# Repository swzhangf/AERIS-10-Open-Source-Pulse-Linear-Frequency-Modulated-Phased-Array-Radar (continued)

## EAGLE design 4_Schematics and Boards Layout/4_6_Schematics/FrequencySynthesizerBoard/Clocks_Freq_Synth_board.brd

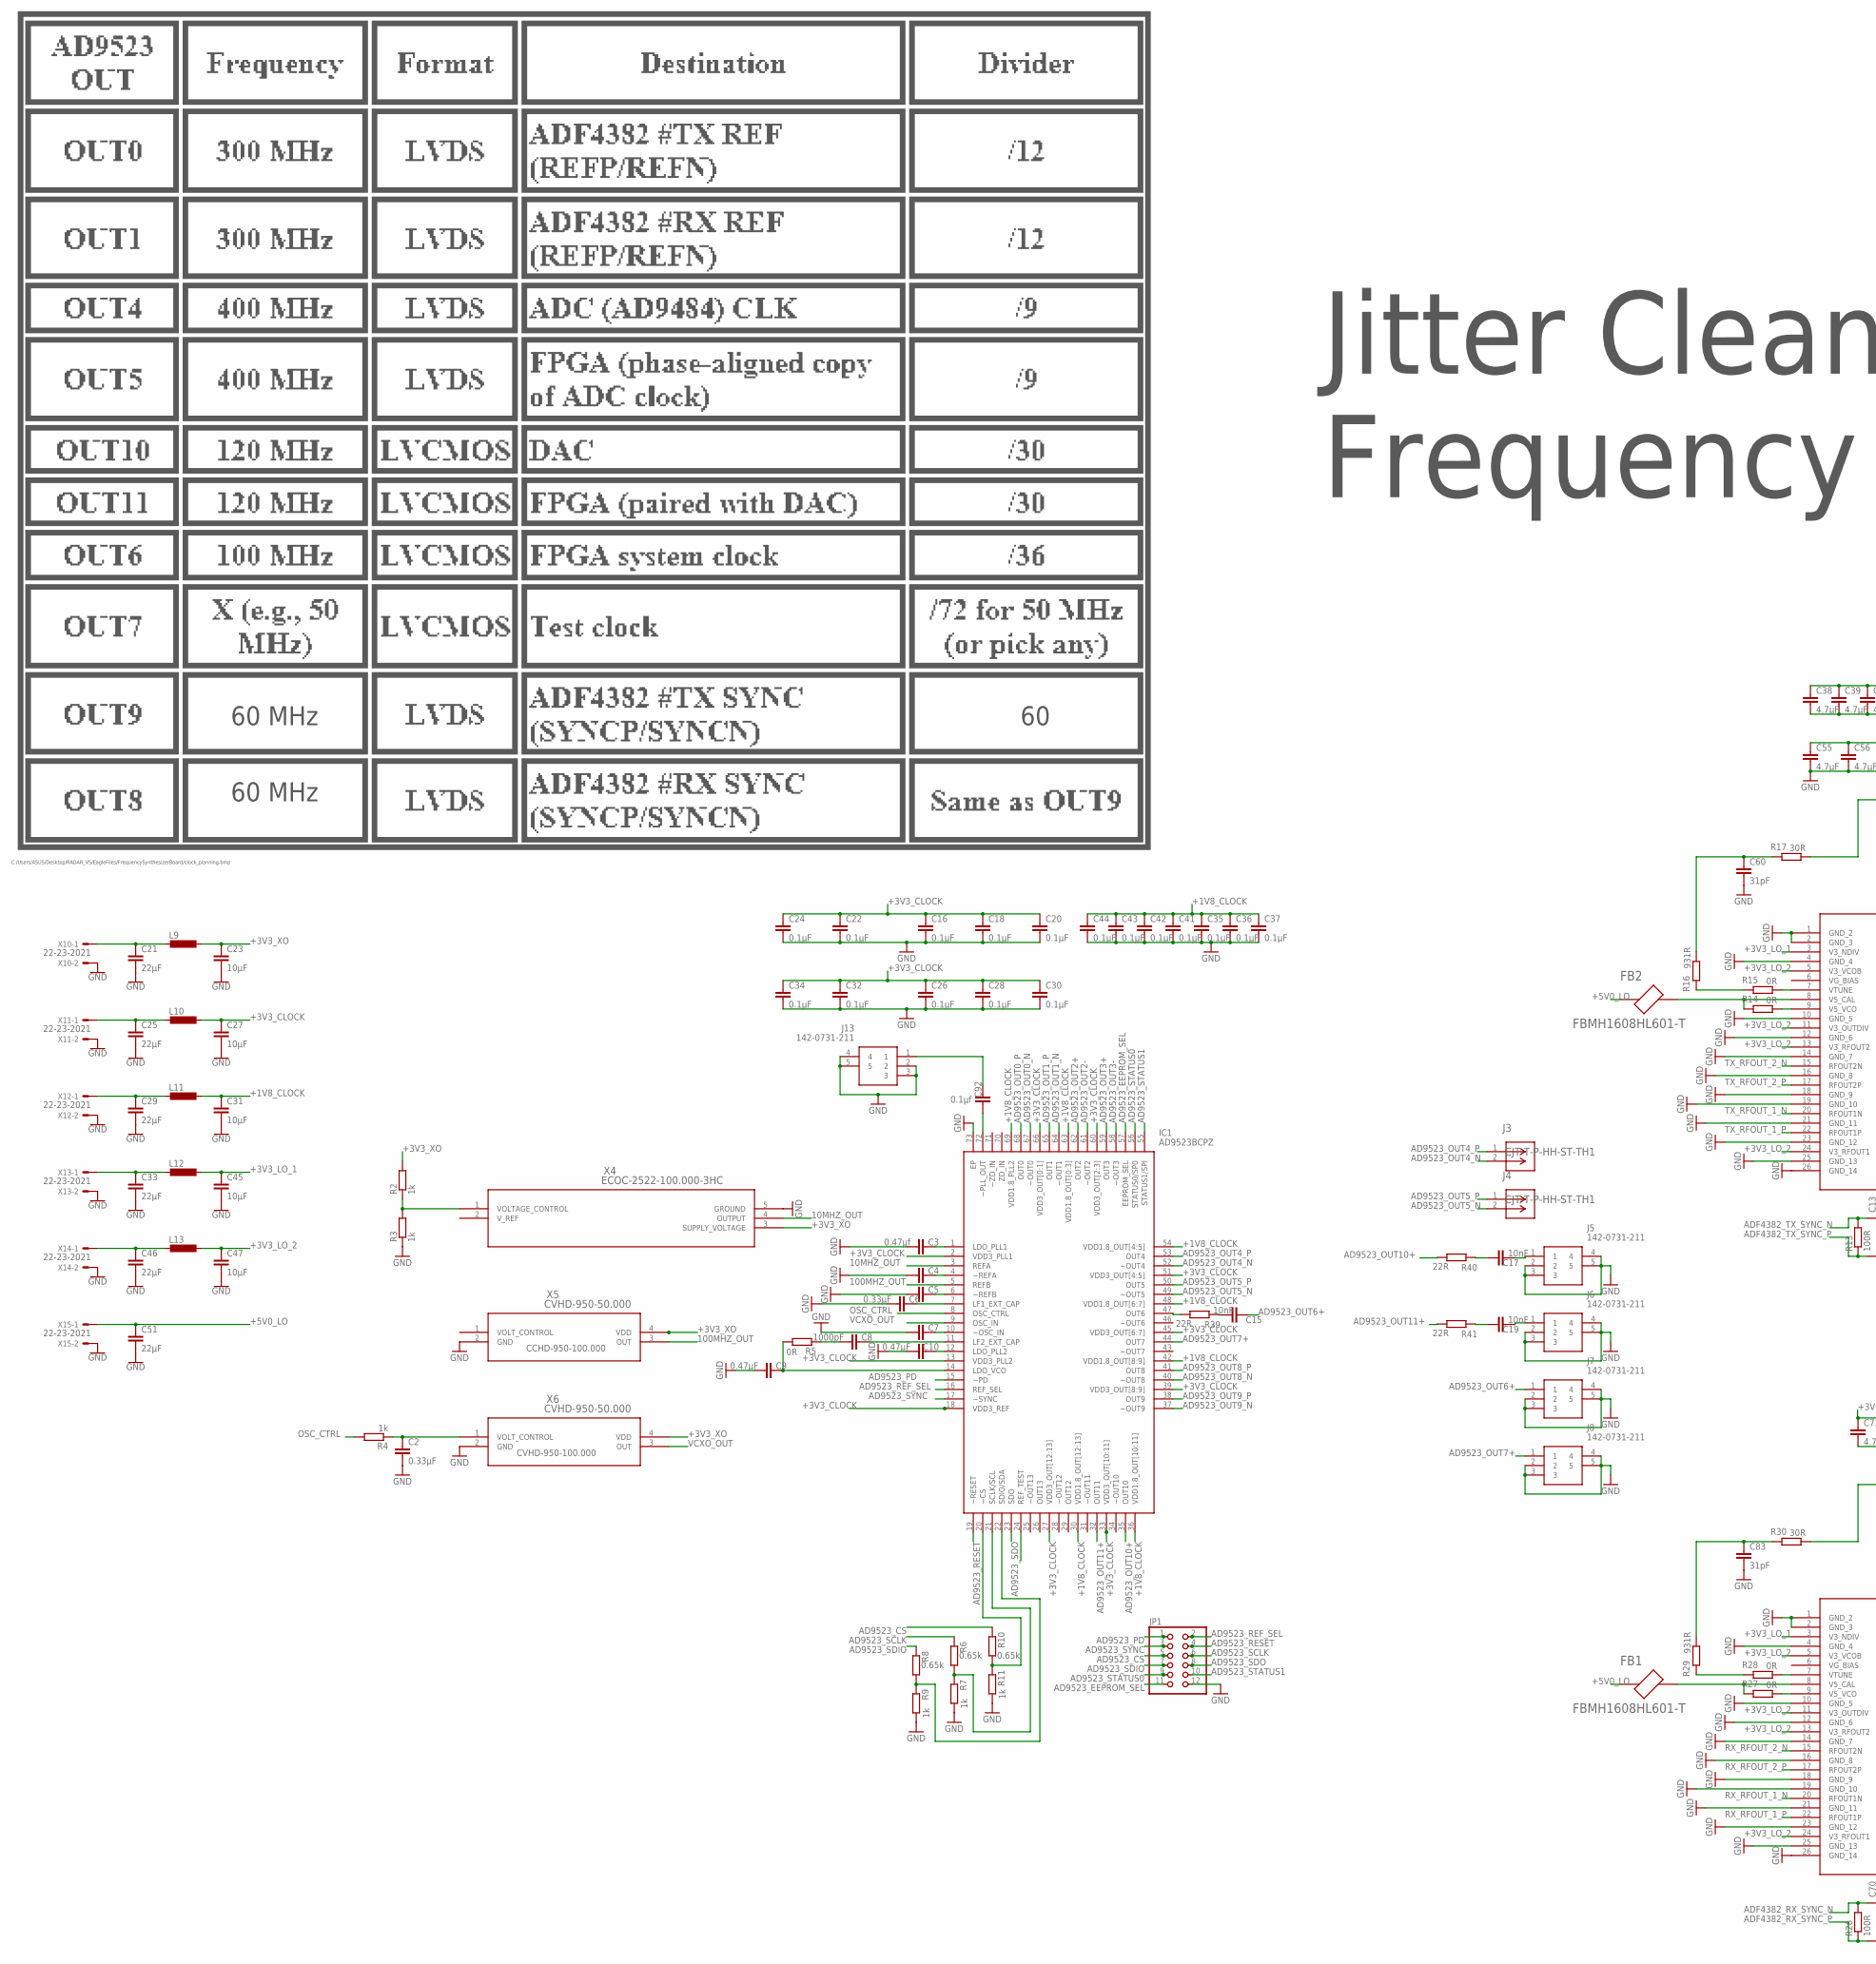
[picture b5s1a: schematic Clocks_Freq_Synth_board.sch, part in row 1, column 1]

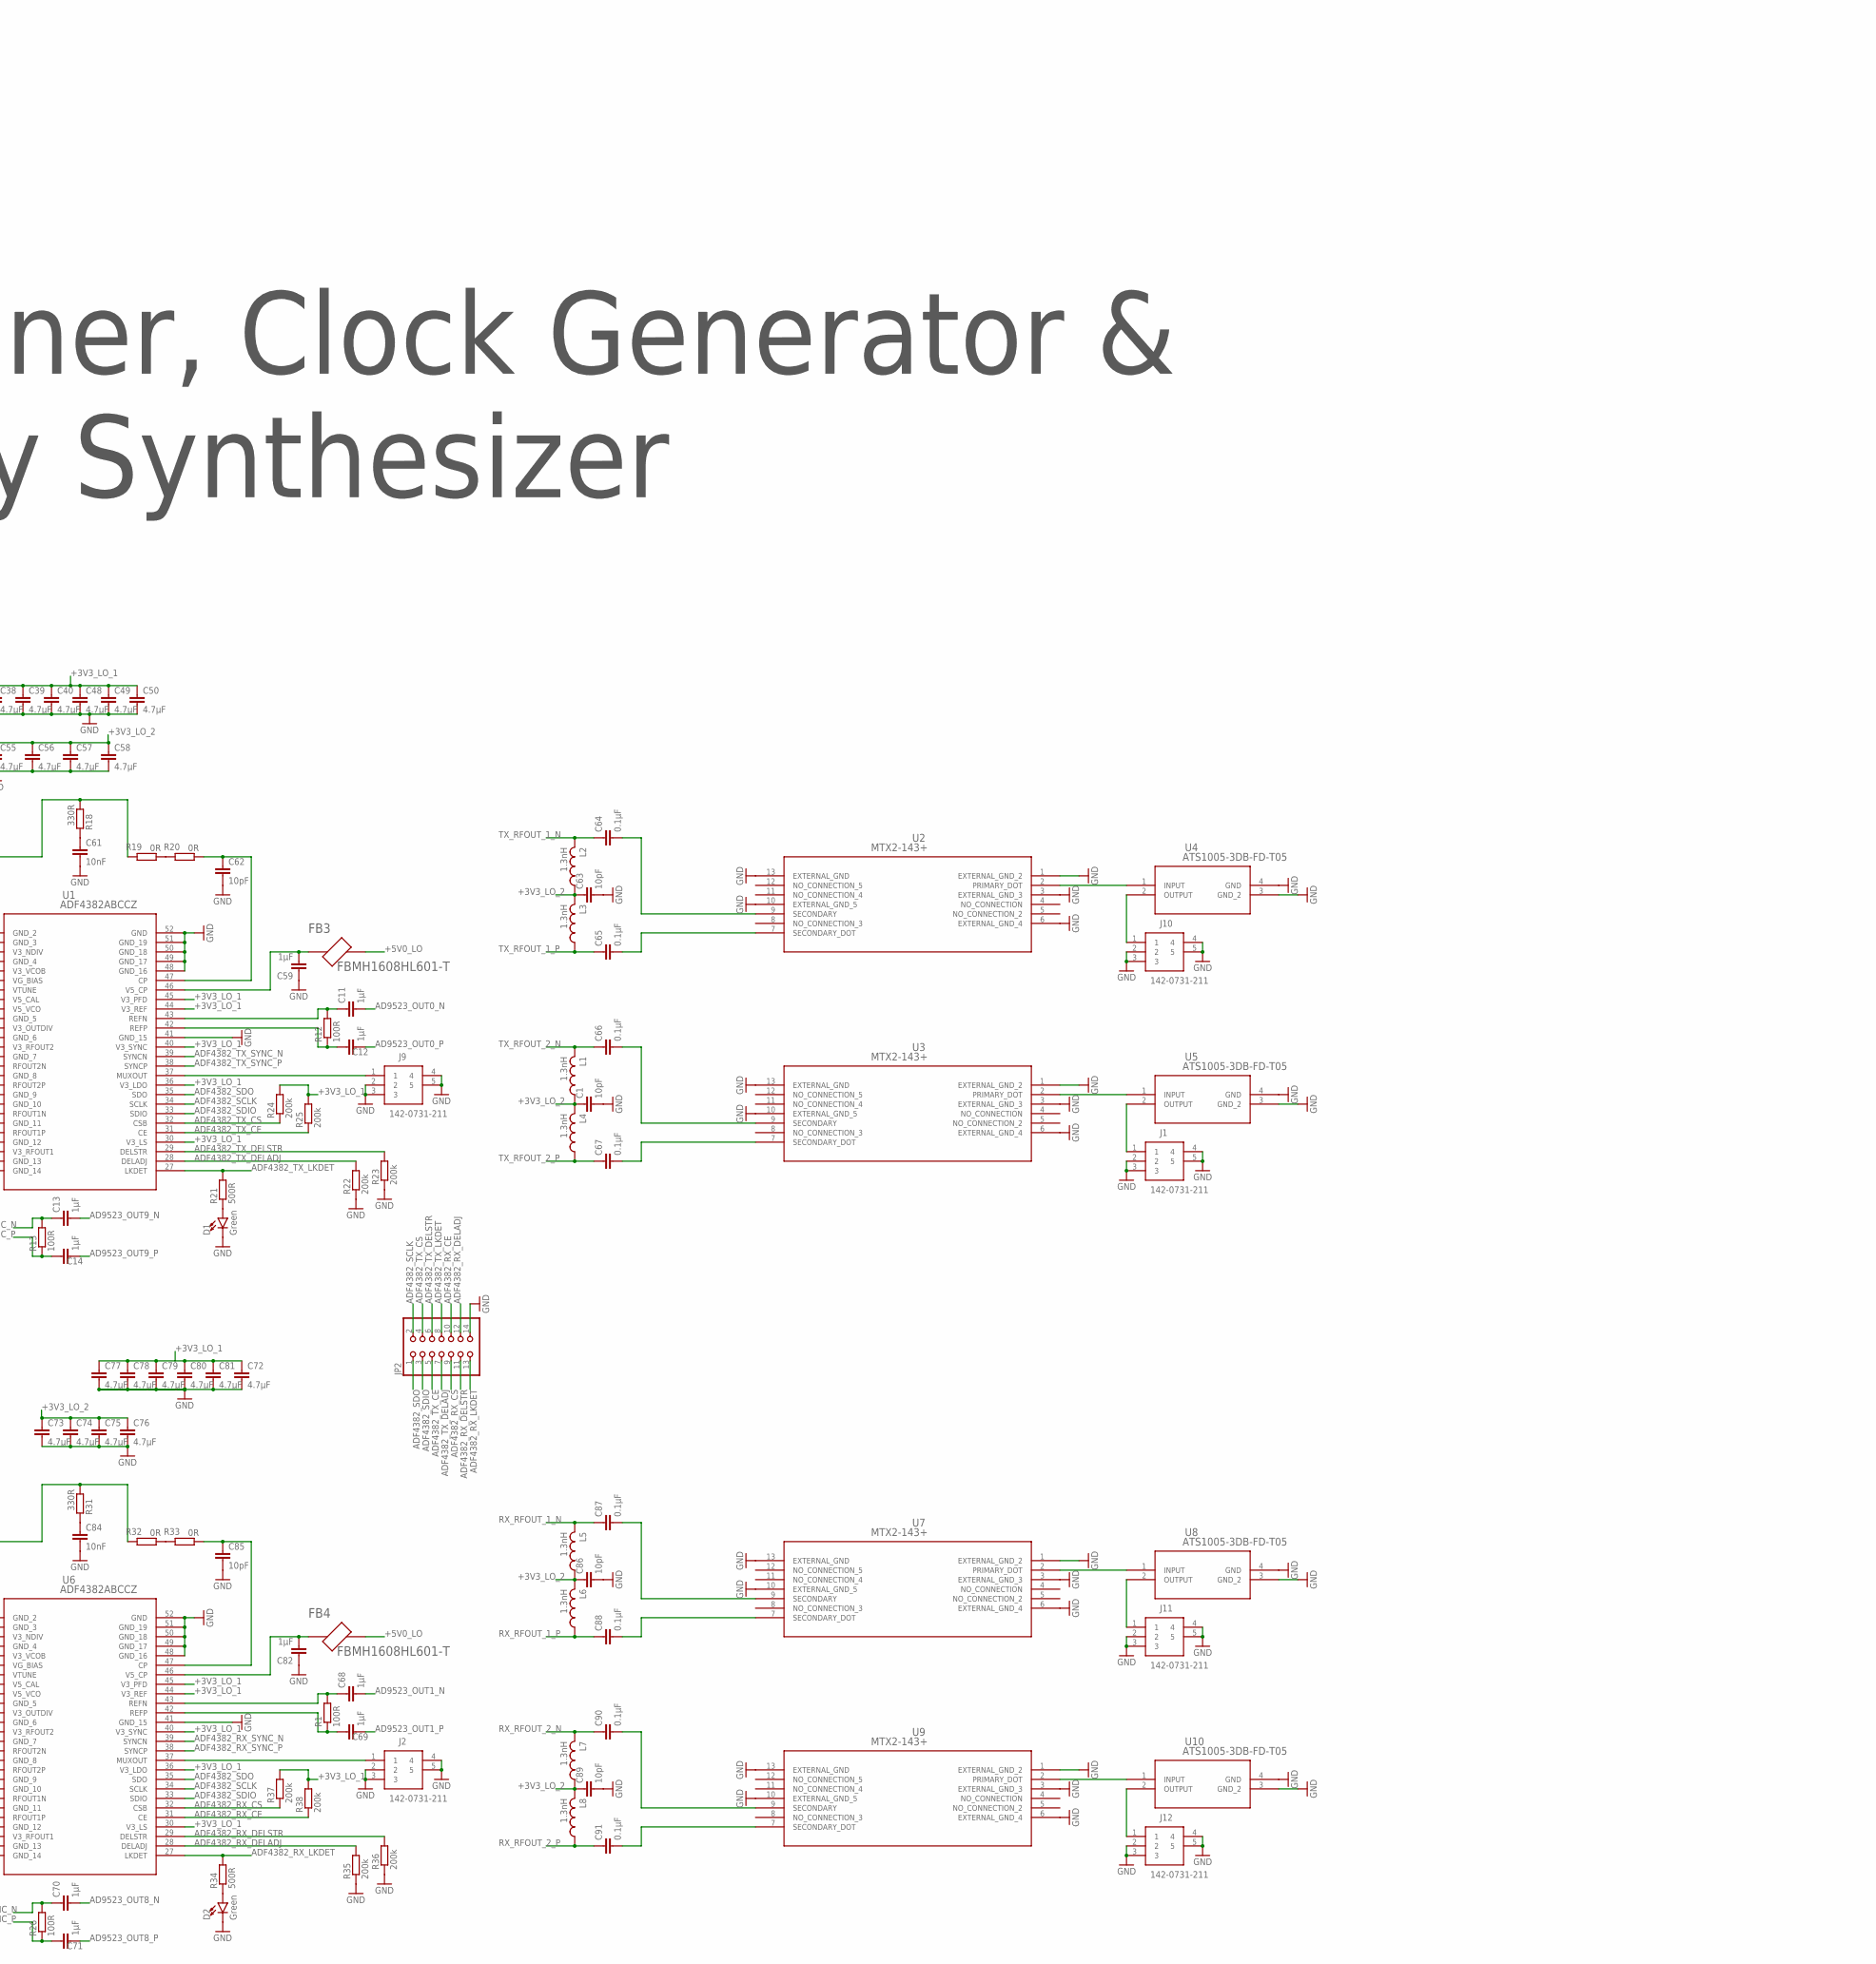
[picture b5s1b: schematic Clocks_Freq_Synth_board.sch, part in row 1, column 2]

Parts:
C1, C62, C63, C85, C86, C89: 10pF; C0201
C2, C6: 0.33µF; C0201
C3: 0.47µf; C0201
C4, C5, C7: C-EUC0201; C0201
C8: 1000pF; C0201
C9, C10: 0.47µF; C0201
C11, C12, C13, C14, C59, C68, C69, C70, C71, C82: 1µF; C0201
C15, C17, C19: 10nF; C0402
C16, C18, C20, C22, C24, C26, C28, C30, C32, C34, C35, C36, C37, C41, C42, C43, C44, C64, C65, C66, C67, C87, C88, C90, C91: 0.1µF; C0201
C21, C25, C29, C33, C46, C51: 22µF; C1210
C23, C27, C31, C45, C47: 10µF; C1210
C38, C39, C40, C48, C49, C50, C55, C56, C57, C58, C72, C73, C74, C75, C76, C77, C78, C79, C80, C81: 4.7µF; C0201
C60, C83: 31pF; C0201
C61, C84: 10nF; C0201
C92: 0.1µf; C0201
D1, D2: Green; LED-0603
FB1, FB2, FB3, FB4: FBMH1608HL601-T; BEADC1608X90N
IC1: AD9523BCPZ; QFN50P1000X1000X100-73N
J1, J2, J5, J6, J7, J8, J9, J10, J11, J12, J13: 142-0731-211; 1420731211
J3, J4: CJT-T-P-HH-ST-TH1; CONN_CJT-T-P-XX-ST-TH1_SAI
JP1: PINHD-2X6; 2X06
JP2: PINHD-2X7; 2X07
L1, L2, L3, L4, L5, L6, L7, L8: 1.3nH; L0201
L9, L10, L11, L12, L13: L-EUL5650M; L5650M
R1, R12, R13, R26: 100R; R0201
R2, R3, R4, R7, R9, R11: 1k; R0201
R5, R14, R15, R19, R20, R27, R28, R32, R33: 0R; R0201
R6, R8, R10: 0.65k; R0201
R16, R29: 931R; R0201
R17, R30: 30R; R0201
R18, R31: 330R; R0201
R21, R34: 500R; R0201
R22, R23, R24, R25, R35, R36, R37, R38: 200k; R0201
R39, R40, R41: 22R; R0201
U1, U6: ADF4382ABCCZ; CC-48-10_ADI
U2, U3, U7, U9: MTX2-143+; DQ1225_MNC
U4, U5, U8, U10: ATS1005-3DB-FD-T05; SMT_DB-FD-T05_SUS
X4: ECOC-2522-100.000-3HC; SMD5_ECOC-2522_25P4X22_ECS
X5, X6: CVHD-950-50.000; SMD4_CVHD-950_CRX
X10, X11, X12, X13, X14, X15: 22-23-2021

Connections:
10MHZ_OUT: IC1.3 (REFA), X4.4 (OUTPUT)
100MHZ_OUT: IC1.5 (REFB), X5.3 (OUT)
+1V8_CLOCK: C31.1, C35.1, C36.1, C37.1, C41.1, C42.1, C43.1, C44.1, IC1.30 (VDD1.8_OUT[12:13]), IC1.36 (VDD1.8_OUT[10:11]), IC1.42 (VDD1.8_OUT[8:9]), IC1.48 (VDD1.8_OUT[6:7]), IC1.54 (VDD1.8_OUT[4:5]), IC1.63 (VDD1.8_OUT[0:3]), IC1.69 (VDD1.8_PLL2), L11.1
+3V3_CLOCK: C16.1, C18.1, C20.1, C22.1, C24.1, C26.1, C27.1, C28.1, C30.1, C32.1, C34.1, IC1.2 (VDD3_PLL1), IC1.13 (VDD3_PLL2), IC1.18 (VDD3_REF), IC1.27 (VDD3_OUT[12:13]), IC1.33 (VDD3_OUT[10:11]), IC1.39 (VDD3_OUT[8:9]), IC1.45 (VDD3_OUT[6:7]), IC1.51 (VDD3_OUT[4:5]), IC1.60 (VDD3_OUT[2:3]), IC1.66 (VDD3_OUT[0:1]), L10.1
+3V3_LO_1: C38.1, C39.1, C40.1, C45.1, C48.1, C49.1, C50.1, C72.1, C77.1, C78.1, C79.1, C80.1, C81.1, L12.1, R24.2, R25.2, R37.2, R38.2, U1.3 (V3_NDIV), U1.30 (V3_LS), U1.36 (V3_LDO), U1.40 (V3_SYNC), U1.44 (V3_REF), U1.45 (V3_PFD), U6.3 (V3_NDIV), U6.30 (V3_LS), U6.36 (V3_LDO), U6.40 (V3_SYNC), U6.44 (V3_REF), U6.45 (V3_PFD)
+3V3_LO_2: C1.1, C47.1, C55.1, C56.1, C57.1, C58.1, C63.1, C73.1, C74.1, C75.1, C76.1, C86.1, C89.1, L1.1, L2.1, L3.2, L4.2, L5.1, L6.2, L7.1, L8.2, L13.1, U1.5 (V3_VCOB), U1.11 (V3_OUTDIV), U1.13 (V3_RFOUT2), U1.24 (V3_RFOUT1), U6.5 (V3_VCOB), U6.11 (V3_OUTDIV), U6.13 (V3_RFOUT2), U6.24 (V3_RFOUT1)
+3V3_XO: C23.1, L9.1, R2.2, X4.3 (SUPPLY_VOLTAGE), X5.4 (VDD), X6.4 (VDD)
+5V0_LO: C51.1, FB1.1, FB2.1, FB3.2, FB4.2, X15.1
AD9523_CS: JP1.5, R10.1
AD9523_EEPROM_SEL: IC1.57 (EEPROM_SEL), JP1.11
AD9523_OUT0_N: C11.2, IC1.67 (~OUT0)
AD9523_OUT0_P: C12.2, IC1.68 (OUT0)
AD9523_OUT1_N: C68.2, IC1.64 (~OUT1)
AD9523_OUT1_P: C69.2, IC1.65 (OUT1)
AD9523_OUT2+: IC1.62 (OUT2)
AD9523_OUT2-: IC1.61 (~OUT2)
AD9523_OUT3+: IC1.59 (OUT3)
AD9523_OUT3-: IC1.58 (~OUT3)
AD9523_OUT4_N: IC1.52 (~OUT4), J3.2
AD9523_OUT4_P: IC1.53 (OUT4), J3.1
AD9523_OUT5_N: IC1.49 (~OUT5), J4.2
AD9523_OUT5_P: IC1.50 (OUT5), J4.1
AD9523_OUT6+: C15.2, J7.1
AD9523_OUT7+: IC1.44 (OUT7), J8.1
AD9523_OUT8_N: C70.2, IC1.40 (~OUT8)
AD9523_OUT8_P: C71.2, IC1.41 (OUT8)
AD9523_OUT9_N: C13.2, IC1.37 (~OUT9)
AD9523_OUT9_P: C14.2, IC1.38 (OUT9)
AD9523_OUT10+: IC1.35 (OUT10), R40.1
AD9523_OUT11+: IC1.32 (OUT11), R41.1
AD9523_PD: IC1.15 (~PD), JP1.1
AD9523_REF_SEL: IC1.16 (REF_SEL), JP1.2
AD9523_RESET: IC1.19 (~RESET), JP1.4
AD9523_SCLK: JP1.6, R6.1
AD9523_SDIO: JP1.7, R8.1
AD9523_SDO: IC1.23 (SDO), JP1.8
AD9523_STATUS0: IC1.56 (STATUS0/SP0), JP1.9
AD9523_STATUS1: IC1.55 (STATUS1/SPI), JP1.10
AD9523_SYNC: IC1.17 (~SYNC), JP1.3
ADF4382_RX_CE: JP2.10, R38.1, U6.31 (CE)
ADF4382_RX_CS: JP2.9, R37.1, U6.32 (CSB)
ADF4382_RX_DELADJ: JP2.12, R35.2, U6.28 (DELADJ)
ADF4382_RX_DELSTR: JP2.11, R36.2, U6.29 (DELSTR)
ADF4382_RX_LKDET: JP2.13, R34.2, U6.27 (LKDET)
ADF4382_RX_SYNC_N: C70.1, R26.2, U6.39 (SYNCN)
ADF4382_RX_SYNC_P: C71.1, R26.1, U6.38 (SYNCP)
ADF4382_SCLK: JP2.2, U1.34 (SCLK), U6.34 (SCLK)
ADF4382_SDIO: JP2.3, U1.33 (SDIO), U6.33 (SDIO)
ADF4382_SDO: JP2.1, U1.35 (SDO), U6.35 (SDO)
ADF4382_TX_CE: JP2.5, R25.1, U1.31 (CE)
ADF4382_TX_CS: JP2.4, R24.1, U1.32 (CSB)
ADF4382_TX_DELADJ: JP2.7, R22.2, U1.28 (DELADJ)
ADF4382_TX_DELSTR: JP2.6, R23.2, U1.29 (DELSTR)
ADF4382_TX_LKDET: JP2.8, R21.2, U1.27 (LKDET)
ADF4382_TX_SYNC_N: C13.1, R13.2, U1.39 (SYNCN)
ADF4382_TX_SYNC_P: C14.1, R13.1, U1.38 (SYNCP)
GND: C1.2, C2.2, C3.1, C4.1, C5.1, C6.1, C7.1, C9.1, C10.1, C16.2, C18.2, C20.2, C21.2, C22.2, C23.2, C24.2, C25.2, C26.2, C27.2, C28.2, C29.2, C30.2, C31.2, C32.2, C33.2, C34.2, C35.2, C36.2, C37.2, C38.2, C39.2, C40.2, C41.2, C42.2, C43.2, C44.2, C45.2, C46.2, C47.2, C48.2, C49.2, C50.2, C51.2, C55.2, C56.2, C57.2, C58.2, C59.1, C60.2, C61.2, C62.2, C63.2, C72.2, C73.2, C74.2, C75.2, C76.2, C77.2, C78.2, C79.2, C80.2, C81.2, C82.1, C83.2, C84.2, C85.2, C86.2, C89.2, D1.C, D2.C, IC1.73 (EP), J1.2, J1.3, J1.4, J1.5, J2.2, J2.3, J2.4, J2.5, J5.2, J5.3, J5.4, J5.5, J6.2, J6.3, J6.4, J6.5, J7.2, J7.3, J7.4, J7.5, J8.2, J8.3, J8.4, J8.5, J9.2, J9.3, J9.4, J9.5, J10.2, J10.3, J10.4, J10.5, J11.2, J11.3, J11.4, J11.5, J12.2, J12.3, J12.4, J12.5, J13.2, J13.3, J13.4, J13.5, JP1.12, JP2.14, R3.1, R7.2, R9.2, R11.2, R22.1, R23.1, R35.1, R36.1, U1.1 (GND_2), U1.2 (GND_3), U1.4 (GND_4), U1.10 (GND_5), U1.12 (GND_6), U1.14 (GND_7), U1.16 (GND_8), U1.18 (GND_9), U1.19 (GND_10), U1.21 (GND_11), U1.23 (GND_12), U1.25 (GND_13), U1.26 (GND_14), U1.41 (GND_15), U1.48 (GND_16), U1.49 (GND_17), U1.50 (GND_18), U1.51 (GND_19), U1.52 (GND), U2.1 (EXTERNAL_GND_2), U2.3 (EXTERNAL_GND_3), U2.6 (EXTERNAL_GND_4), U2.10 (EXTERNAL_GND_5), U2.13 (EXTERNAL_GND), U3.1 (EXTERNAL_GND_2), U3.3 (EXTERNAL_GND_3), U3.6 (EXTERNAL_GND_4), U3.10 (EXTERNAL_GND_5), U3.13 (EXTERNAL_GND), U4.3 (GND_2), U4.4 (GND), U5.3 (GND_2), U5.4 (GND), U6.1 (GND_2), U6.2 (GND_3), U6.4 (GND_4), U6.10 (GND_5), U6.12 (GND_6), U6.14 (GND_7), U6.16 (GND_8), U6.18 (GND_9), U6.19 (GND_10), U6.21 (GND_11), U6.23 (GND_12), U6.25 (GND_13), U6.26 (GND_14), U6.41 (GND_15), U6.48 (GND_16), U6.49 (GND_17), U6.50 (GND_18), U6.51 (GND_19), U6.52 (GND), U7.1 (EXTERNAL_GND_2), U7.3 (EXTERNAL_GND_3), U7.6 (EXTERNAL_GND_4), U7.10 (EXTERNAL_GND_5), U7.13 (EXTERNAL_GND), U8.3 (GND_2), U8.4 (GND), U9.1 (EXTERNAL_GND_2), U9.3 (EXTERNAL_GND_3), U9.6 (EXTERNAL_GND_4), U9.10 (EXTERNAL_GND_5), U9.13 (EXTERNAL_GND), U10.3 (GND_2), U10.4 (GND), X4.5 (GROUND), X5.2 (GND), X6.2 (GND), X10.2, X11.2, X12.2, X13.2, X14.2, X15.2
unnamed: R2.1, R3.2, X4.1 (VOLTAGE_CONTROL)
unnamed: C2.1, R4.1, X6.1 (VOLT_CONTROL)
unnamed: C3.2, IC1.1 (LDO_PLL1)
unnamed: C6.2, IC1.7 (LF1_EXT_CAP)
unnamed: C4.2, IC1.4 (~REFA)
unnamed: C5.2, IC1.6 (~REFB)
unnamed: C7.2, IC1.10 (~OSC_IN)
unnamed: C8.2, IC1.11 (LF2_EXT_CAP)
unnamed: C8.1, R5.1
unnamed: C9.2, IC1.14 (LDO_VCO), R5.2
unnamed: C10.2, IC1.12 (LDO_PLL2)
unnamed: IC1.21 (SCLK/SCL), R6.2, R7.1
unnamed: IC1.22 (SDIO/SDA), R8.2, R9.1
unnamed: IC1.20 (~CS), R10.2, R11.1
unnamed: C11.1, R12.2, U1.43 (REFN)
unnamed: C12.1, R12.1, U1.42 (REFP)
unnamed: C61.1, R18.2
unnamed: R14.1, U1.9 (V5_VCO)
unnamed: FB2.2, R14.2, U1.8 (V5_CAL)
unnamed: C59.2, FB3.1, U1.46 (V5_CP)
unnamed: R19.1, R20.2
unnamed: R15.1, U1.7 (VTUNE)
unnamed: R15.2, R16.2
unnamed: C60.1, R16.1, R17.2
unnamed: R17.1, R18.1, R19.2
unnamed: C62.1, R20.1, U1.47 (CP)
unnamed: U2.2 (PRIMARY_DOT), U4.1 (INPUT)
unnamed: C65.2, U2.7 (SECONDARY_DOT)
unnamed: J10.1, U4.2 (OUTPUT)
unnamed: C64.2, U2.9 (SECONDARY)
unnamed: C67.2, U3.7 (SECONDARY_DOT)
unnamed: C66.2, U3.9 (SECONDARY)
unnamed: U3.2 (PRIMARY_DOT), U5.1 (INPUT)
unnamed: J1.1, U5.2 (OUTPUT)
unnamed: D1.A, R21.1
unnamed: J9.1, U1.37 (MUXOUT)
unnamed: C68.1, R1.2, U6.43 (REFN)
unnamed: C69.1, R1.1, U6.42 (REFP)
unnamed: R27.1, U6.9 (V5_VCO)
unnamed: FB1.2, R27.2, U6.8 (V5_CAL)
unnamed: C82.2, FB4.1, U6.46 (V5_CP)
unnamed: C84.1, R31.2
unnamed: R32.1, R33.2
unnamed: R28.1, U6.7 (VTUNE)
unnamed: R28.2, R29.2
unnamed: C83.1, R29.1, R30.2
unnamed: R30.1, R31.1, R32.2
unnamed: C85.1, R33.1, U6.47 (CP)
unnamed: D2.A, R34.1
unnamed: J2.1, U6.37 (MUXOUT)
unnamed: C88.2, U7.7 (SECONDARY_DOT)
unnamed: C87.2, U7.9 (SECONDARY)
unnamed: U7.2 (PRIMARY_DOT), U8.1 (INPUT)
unnamed: J11.1, U8.2 (OUTPUT)
unnamed: C91.2, U9.7 (SECONDARY_DOT)
unnamed: C90.2, U9.9 (SECONDARY)
unnamed: U9.2 (PRIMARY_DOT), U10.1 (INPUT)
unnamed: J12.1, U10.2 (OUTPUT)
unnamed: C92.1, IC1.72 (~PLL_OUT)
unnamed: C92.2, J13.1
unnamed: IC1.47 (OUT6), R39.1
unnamed: C15.1, R39.2
unnamed: C17.2, J5.1
unnamed: C17.1, R40.2
unnamed: C19.2, J6.1
unnamed: C19.1, R41.2
unnamed: C21.1, L9.2, X10.1
unnamed: C25.1, L10.2, X11.1
unnamed: C29.1, L11.2, X12.1
unnamed: C33.1, L12.2, X13.1
unnamed: C46.1, L13.2, X14.1
OSC_CTRL: IC1.8 (OSC_CTRL), R4.2
RX_RFOUT_1_N: C87.1, L5.2, U6.20 (RFOUT1N)
RX_RFOUT_1_P: C88.1, L6.1, U6.22 (RFOUT1P)
RX_RFOUT_2_N: C90.1, L7.2, U6.15 (RFOUT2N)
RX_RFOUT_2_P: C91.1, L8.1, U6.17 (RFOUT2P)
TX_RFOUT_1_N: C64.1, L2.2, U1.20 (RFOUT1N)
TX_RFOUT_1_P: C65.1, L3.1, U1.22 (RFOUT1P)
TX_RFOUT_2_N: C66.1, L1.2, U1.15 (RFOUT2N)
TX_RFOUT_2_P: C67.1, L4.1, U1.17 (RFOUT2P)
VCXO_OUT: IC1.9 (OSC_IN), X6.3 (OUT)

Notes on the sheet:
CCHD-950-100.000
CVHD-950-100.000
Jitter Cleaner, Clock Generator & Frequency Synthesizer
C:/Users/ASUS/Desktop/RADAR_V5/EagleFiles/FrequencySynthesizerBoard/clock_planning.bmp
60 MHz

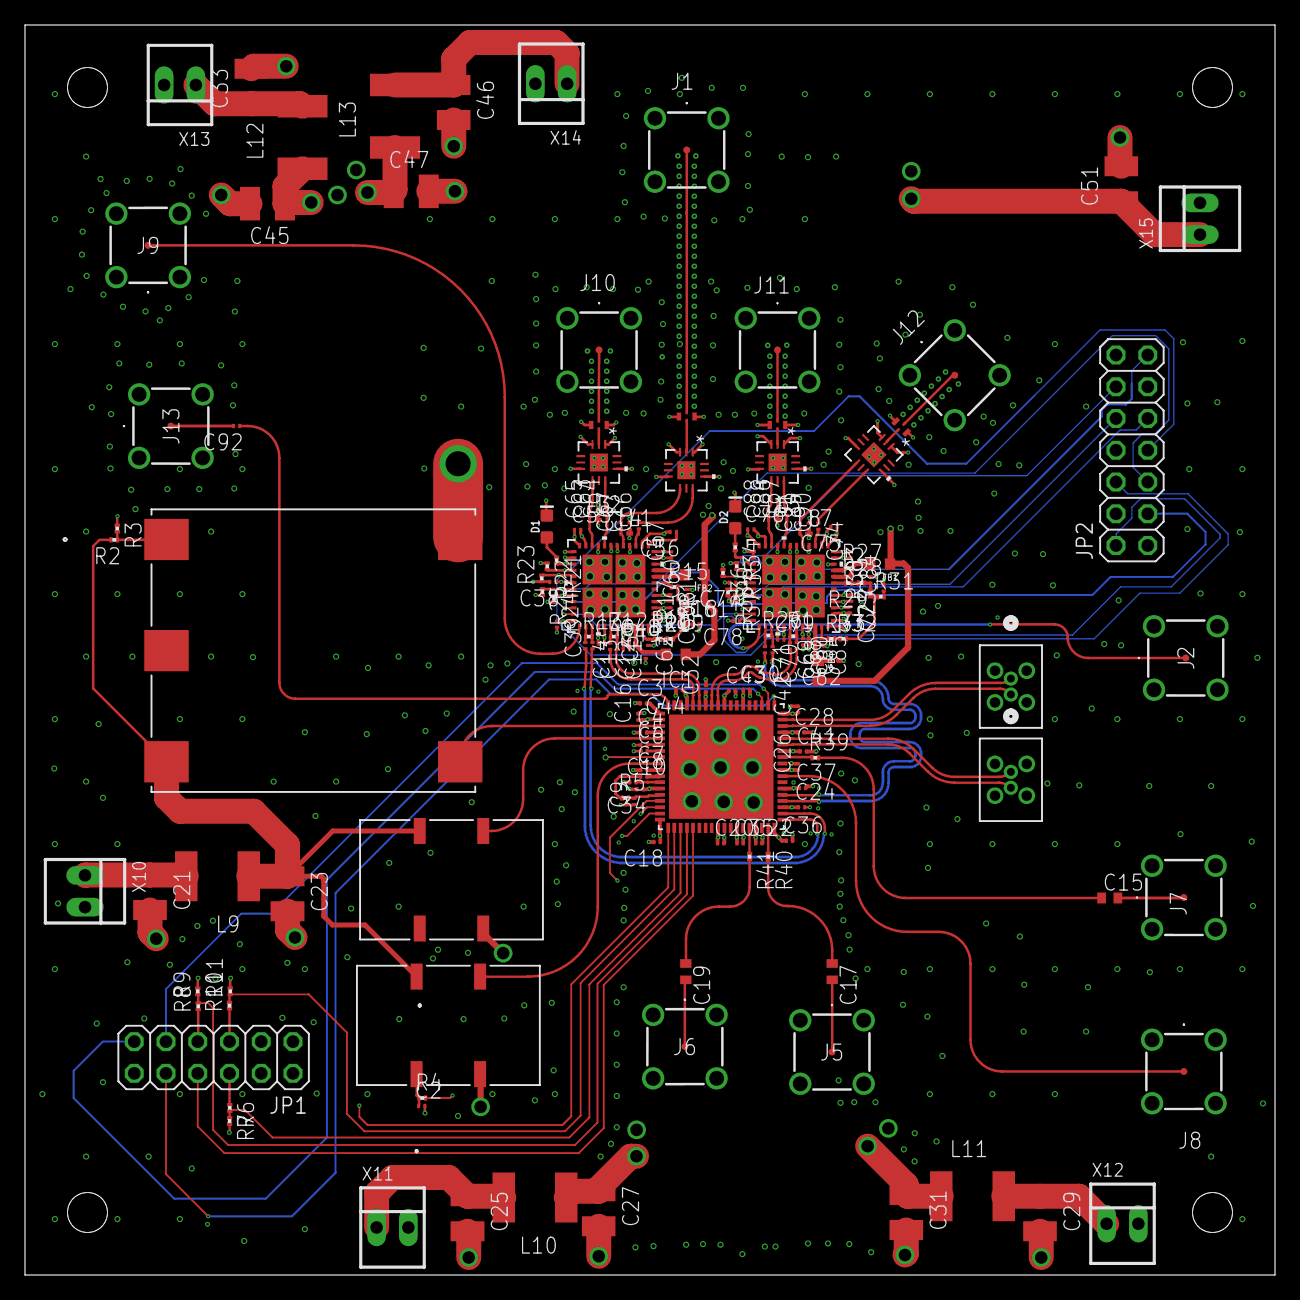
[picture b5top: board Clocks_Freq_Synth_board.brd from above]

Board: 6 copper layers, 100.0 x 100.0 mm, 184 parts (0 on the bottom side), 134 nets.

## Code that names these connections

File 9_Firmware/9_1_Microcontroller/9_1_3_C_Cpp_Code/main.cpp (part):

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};

// Convenience HAL wrappers for AD9523 control pins (GPIOF as you said)
static inline void AD9523_PD(bool v)        { HAL_GPIO_WritePin(GPIOF, AD9523_PD_Pin, v ? GPIO_PIN_SET : GPIO_PIN_RESET); }
static inline void AD9523_REF_SEL(bool v)   { HAL_GPIO_WritePin(GPIOF, AD9523_REF_SEL_Pin, v ? GPIO_PIN_SET : GPIO_PIN_RESET); }
static inline void AD9523_SYNC_PULSE(void)  { HAL_GPIO_WritePin(GPIOF, AD9523_SYNC_Pin, GPIO_PIN_SET); HAL_Delay(1); HAL_GPIO_WritePin(GPIOF, AD9523_SYNC_Pin, GPIO_PIN_RESET); }
static inline void AD9523_RESET_ASSERT()    { HAL_GPIO_WritePin(GPIOF, AD9523_RESET_Pin, GPIO_PIN_RESET); } // check polarity
static inline void AD9523_RESET_RELEASE()   { HAL_GPIO_WritePin(GPIOF, AD9523_RESET_Pin, GPIO_PIN_SET); }
static inline void AD9523_CS(bool v)        { HAL_GPIO_WritePin(GPIOF, AD9523_CS_Pin, v ? GPIO_PIN_SET : GPIO_PIN_RESET); }
static inline void AD9523_EEPROM_SEL(bool v){ HAL_GPIO_WritePin(GPIOF, AD9523_EEPROM_SEL_Pin, v ? GPIO_PIN_SET : GPIO_PIN_RESET); }

/* USER CODE END PV */

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    HAL_Delay(10);

    // Step 2: Disable PA power supplies
    DIAG("PWR", "Step 2: Disable PA 5V supplies (EN_P_5V0_PA1/PA2/PA3 LOW)");
    HAL_GPIO_WritePin(EN_P_5V0_PA1_GPIO_Port, EN_P_5V0_PA1_Pin | EN_P_5V0_PA2_Pin | EN_P_5V0_PA3_Pin, GPIO_PIN_RESET);
    HAL_Delay(10);

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    // 1. Check AD9523 Clock Generator
    static uint32_t last_clock_check = 0;
    if (HAL_GetTick() - last_clock_check > 5000) {
        GPIO_PinState s0 = HAL_GPIO_ReadPin(AD9523_STATUS0_GPIO_Port, AD9523_STATUS0_Pin);
        GPIO_PinState s1 = HAL_GPIO_ReadPin(AD9523_STATUS1_GPIO_Port, AD9523_STATUS1_Pin);
        DIAG_GPIO("CLK", "AD9523 STATUS0", s0);
        DIAG_GPIO("CLK", "AD9523 STATUS1", s1);
        if (s0 == GPIO_PIN_RESET || s1 == GPIO_PIN_RESET) {
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    DIAG_ERR("PA", "Disabling TX mixers (GPIOD pin 11 LOW)");
    HAL_GPIO_WritePin(GPIOD, GPIO_PIN_11, GPIO_PIN_RESET);

    DIAG_ERR("PA", "Cutting PA 5V supplies (PA1/PA2/PA3 LOW)");
    HAL_GPIO_WritePin(EN_P_5V0_PA1_GPIO_Port, EN_P_5V0_PA1_Pin, GPIO_PIN_RESET);
    HAL_GPIO_WritePin(EN_P_5V0_PA2_GPIO_Port, EN_P_5V0_PA2_Pin, GPIO_PIN_RESET);
    HAL_GPIO_WritePin(EN_P_5V0_PA3_GPIO_Port, EN_P_5V0_PA3_Pin, GPIO_PIN_RESET);
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
  DIAG_SECTION("AD9523 POWER SEQUENCING");
  DIAG("PWR", "Asserting AD9523 reset (pin LOW)");
  HAL_GPIO_WritePin(AD9523_RESET_GPIO_Port,AD9523_RESET_Pin,GPIO_PIN_RESET);

  //Power sequencing AD9523
  DIAG("PWR", "Enabling 1.8V clock rail");
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  HAL_GPIO_WritePin(EN_P_3V3_CLOCK_GPIO_Port,EN_P_3V3_CLOCK_Pin,GPIO_PIN_SET);
  HAL_Delay(100);
  DIAG("PWR", "Releasing AD9523 reset (pin HIGH)");
  HAL_GPIO_WritePin(AD9523_RESET_GPIO_Port,AD9523_RESET_Pin,GPIO_PIN_SET);
  HAL_Delay(100);
  DIAG("PWR", "AD9523 power sequencing complete -- all rails up, reset released");

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
  // check if there is a lock via direct GPIO (independent of register read above)
  DIAG("LO", "Direct GPIO lock detect pins:");
  DIAG_GPIO("LO", "ADF4382_TX_LKDET", ADF4382_TX_LKDET_GPIO_Port, ADF4382_TX_LKDET_Pin);
  DIAG_GPIO("LO", "ADF4382_RX_LKDET", ADF4382_RX_LKDET_GPIO_Port, ADF4382_RX_LKDET_Pin);
  if(HAL_GPIO_ReadPin (ADF4382_TX_LKDET_GPIO_Port, ADF4382_TX_LKDET_Pin))
  {
      // Set The LED_1 ON!
      HAL_GPIO_WritePin(LED_1_GPIO_Port, LED_1_Pin, GPIO_PIN_SET);
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      DIAG_WARN("LO", "TX NOT locked via GPIO -- LED_1 OFF");
  }

  if(HAL_GPIO_ReadPin (ADF4382_RX_LKDET_GPIO_Port, ADF4382_RX_LKDET_Pin))
  {
      // Set The LED_2 ON!
      HAL_GPIO_WritePin(LED_2_GPIO_Port, LED_2_Pin, GPIO_PIN_SET);
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	  /* DAC1: Address 0b1001000 = 0x48 */
	  DIAG("PA", "Initializing DAC1 (I2C1, addr=0x48, 8-bit)");
	  if (!DAC5578_Init(&hdac1, &hi2c1, 0x48, 8,
			  DAC_1_VG_LDAC_GPIO_Port, DAC_1_VG_LDAC_Pin,
			  DAC_1_VG_CLR_GPIO_Port, DAC_1_VG_CLR_Pin)) {
		  DIAG_ERR("PA", "DAC1 init FAILED -- calling Error_Handler()");
		  Error_Handler();
	  }
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	  /* DAC2: Address 0b1001001 = 0x49 */
	  DIAG("PA", "Initializing DAC2 (I2C1, addr=0x49, 8-bit)");
	  if (!DAC5578_Init(&hdac2, &hi2c1, 0x49, 8,
			  DAC_2_VG_LDAC_GPIO_Port, DAC_2_VG_LDAC_Pin,
			  DAC_2_VG_CLR_GPIO_Port, DAC_2_VG_CLR_Pin)) {
		  DIAG_ERR("PA", "DAC2 init FAILED -- calling Error_Handler()");
		  Error_Handler();
	  }
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
	  /* Optional: Use hardware LDAC for simultaneous update of all channels */
	  DIAG("PA", "Pulsing LDAC on both DACs for simultaneous update");
	  HAL_GPIO_WritePin(DAC_1_VG_LDAC_GPIO_Port, DAC_1_VG_LDAC_Pin, GPIO_PIN_RESET);
	  HAL_GPIO_WritePin(DAC_2_VG_LDAC_GPIO_Port, DAC_2_VG_LDAC_Pin, GPIO_PIN_RESET);
	  HAL_Delay(1);
	  HAL_GPIO_WritePin(DAC_1_VG_LDAC_GPIO_Port, DAC_1_VG_LDAC_Pin, GPIO_PIN_SET);
	  HAL_GPIO_WritePin(DAC_2_VG_LDAC_GPIO_Port, DAC_2_VG_LDAC_Pin, GPIO_PIN_SET);

	  //Enable RF Power Amplifier VDD = 22V
	  DIAG("PA", "Enabling RFPA VDD=22V (EN_DIS_RFPA_VDD HIGH)");
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              DIAG_ERR("LO", "Lock LOST in main loop! TX=%s RX=%s",
                       tx_locked ? "LOCKED" : "UNLOCKED",
                       rx_locked ? "LOCKED" : "UNLOCKED");
              DIAG_GPIO("LO", "TX_LKDET (direct)", ADF4382_TX_LKDET_GPIO_Port, ADF4382_TX_LKDET_Pin);
              DIAG_GPIO("LO", "RX_LKDET (direct)", ADF4382_RX_LKDET_GPIO_Port, ADF4382_RX_LKDET_Pin);
          } else {
              DIAG("LO", "Lock poll OK: TX=LOCKED RX=LOCKED");
          }
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
      runRadarPulseSequence();

      /* [AGC] Outer-loop AGC: sync enable from FPGA via DIG_6 (PD14),
       * then read saturation flag (DIG_5 / PD13) and adjust ADAR1000 VGA
       * common gain once per radar frame (~258 ms).
       * FPGA register host_agc_enable is the single source of truth —
       * DIG_6 propagates it to MCU every frame.
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  __HAL_RCC_GPIOD_CLK_ENABLE();

  /*Configure GPIO pin Output Level */
  HAL_GPIO_WritePin(GPIOF, AD9523_PD_Pin|AD9523_REF_SEL_Pin|AD9523_SYNC_Pin|AD9523_RESET_Pin
                          |AD9523_CS_Pin|AD9523_EEPROM_SEL_Pin|LED_1_Pin|LED_2_Pin
                          |LED_3_Pin|LED_4_Pin, GPIO_PIN_RESET);

  /*Configure GPIO pin Output Level */
  HAL_GPIO_WritePin(GPIOA, ADAR_1_CS_3V3_Pin|ADAR_2_CS_3V3_Pin|ADAR_3_CS_3V3_Pin|ADAR_4_CS_3V3_Pin, GPIO_PIN_RESET);

  /*Configure GPIO pin Output Level */
  HAL_GPIO_WritePin(GPIOG, EN_P_5V0_PA1_Pin|EN_P_5V0_PA2_Pin|EN_P_5V0_PA3_Pin|EN_P_5V5_PA_Pin
                          |EN_P_1V8_CLOCK_Pin|EN_P_3V3_CLOCK_Pin|ADF4382_RX_DELADJ_Pin|ADF4382_RX_DELSTR_Pin
                          |ADF4382_RX_CE_Pin|ADF4382_RX_CS_Pin|ADF4382_TX_DELSTR_Pin|ADF4382_TX_DELADJ_Pin
                          |ADF4382_TX_CS_Pin|ADF4382_TX_CE_Pin, GPIO_PIN_RESET);

  /*Configure GPIO pin Output Level */
  HAL_GPIO_WritePin(GPIOE, EN_P_1V0_FPGA_Pin|EN_P_1V8_FPGA_Pin|EN_P_3V3_FPGA_Pin|EN_P_5V0_ADAR_Pin
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                          |STEPPER_CW_P_Pin|STEPPER_CLK_P_Pin|EN_DIS_RFPA_VDD_Pin|EN_DIS_COOLING_Pin, GPIO_PIN_RESET);

  /*Configure GPIO pin Output Level */
  HAL_GPIO_WritePin(GPIOB, DAC_1_VG_CLR_Pin|DAC_1_VG_LDAC_Pin|DAC_2_VG_CLR_Pin|DAC_2_VG_LDAC_Pin, GPIO_PIN_RESET);

  /*Configure GPIO pins : AD9523_PD_Pin AD9523_REF_SEL_Pin AD9523_SYNC_Pin AD9523_RESET_Pin
                           AD9523_CS_Pin AD9523_EEPROM_SEL_Pin LED_1_Pin LED_2_Pin
                           LED_3_Pin LED_4_Pin */
  GPIO_InitStruct.Pin = AD9523_PD_Pin|AD9523_REF_SEL_Pin|AD9523_SYNC_Pin|AD9523_RESET_Pin
                          |AD9523_CS_Pin|AD9523_EEPROM_SEL_Pin|LED_1_Pin|LED_2_Pin
                          |LED_3_Pin|LED_4_Pin;
  GPIO_InitStruct.Mode = GPIO_MODE_OUTPUT_PP;
  GPIO_InitStruct.Pull = GPIO_NOPULL;
  GPIO_InitStruct.Speed = GPIO_SPEED_FREQ_LOW;
  HAL_GPIO_Init(GPIOF, &GPIO_InitStruct);

  /*Configure GPIO pins : AD9523_STATUS0_Pin AD9523_STATUS1_Pin */
  GPIO_InitStruct.Pin = AD9523_STATUS0_Pin|AD9523_STATUS1_Pin;
  GPIO_InitStruct.Mode = GPIO_MODE_INPUT;
  GPIO_InitStruct.Pull = GPIO_NOPULL;
  HAL_GPIO_Init(GPIOF, &GPIO_InitStruct);

  /*Configure GPIO pins : ADAR_1_CS_3V3_Pin ADAR_2_CS_3V3_Pin ADAR_3_CS_3V3_Pin ADAR_4_CS_3V3_Pin */
  GPIO_InitStruct.Pin = ADAR_1_CS_3V3_Pin|ADAR_2_CS_3V3_Pin|ADAR_3_CS_3V3_Pin|ADAR_4_CS_3V3_Pin;
  GPIO_InitStruct.Mode = GPIO_MODE_OUTPUT_PP;
  GPIO_InitStruct.Pull = GPIO_NOPULL;
  GPIO_InitStruct.Speed = GPIO_SPEED_FREQ_LOW;
  HAL_GPIO_Init(GPIOA, &GPIO_InitStruct);

  /*Configure GPIO pins : EN_P_5V0_PA1_Pin EN_P_5V0_PA2_Pin EN_P_5V0_PA3_Pin EN_P_5V5_PA_Pin
                           EN_P_1V8_CLOCK_Pin EN_P_3V3_CLOCK_Pin ADF4382_RX_DELADJ_Pin ADF4382_RX_DELSTR_Pin
                           ADF4382_RX_CE_Pin ADF4382_RX_CS_Pin ADF4382_TX_DELSTR_Pin ADF4382_TX_DELADJ_Pin
                           ADF4382_TX_CS_Pin ADF4382_TX_CE_Pin */
  GPIO_InitStruct.Pin = EN_P_5V0_PA1_Pin|EN_P_5V0_PA2_Pin|EN_P_5V0_PA3_Pin|EN_P_5V5_PA_Pin
                          |EN_P_1V8_CLOCK_Pin|EN_P_3V3_CLOCK_Pin|ADF4382_RX_DELADJ_Pin|ADF4382_RX_DELSTR_Pin
                          |ADF4382_RX_CE_Pin|ADF4382_RX_CS_Pin|ADF4382_TX_DELSTR_Pin|ADF4382_TX_DELADJ_Pin
                          |ADF4382_TX_CS_Pin|ADF4382_TX_CE_Pin;
  GPIO_InitStruct.Mode = GPIO_MODE_OUTPUT_PP;
  GPIO_InitStruct.Pull = GPIO_NOPULL;
  GPIO_InitStruct.Speed = GPIO_SPEED_FREQ_LOW;
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
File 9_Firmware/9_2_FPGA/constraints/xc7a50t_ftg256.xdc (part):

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# CLOCK CONSTRAINTS
# ============================================================================

# 100MHz System Clock (AD9523 OUT6 → FPGA_SYS_CLOCK → Bank 15 MRCC pin E12)
set_property PACKAGE_PIN E12 [get_ports {clk_100m}]
set_property IOSTANDARD LVCMOS33 [get_ports {clk_100m}]
create_clock -name clk_100m -period 10.0 [get_ports {clk_100m}]
set_input_jitter [get_clocks clk_100m] 0.1

# 120MHz DAC Clock (AD9523 OUT11 → FPGA_DAC_CLOCK → Bank 15 MRCC pin D13)
# NOTE: The physical DAC (U3, AD9708) receives its clock directly from the
#       AD9523 via a separate net (DAC_CLOCK), NOT from the FPGA. The FPGA
#       uses this clock input for internal DAC data timing only. The RTL port
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# banks. IBUFDS input buffers are VCCO-independent — they work correctly even
# with VCCO=3.3V. The BIVC-1 DRC (voltage conflict with LVCMOS33 adc_pwdn)
# is waived in the build script since this bank has only LVDS *inputs*.
set_property PACKAGE_PIN N14 [get_ports {adc_dco_p}]
set_property PACKAGE_PIN P14 [get_ports {adc_dco_n}]
set_property IOSTANDARD LVDS_25 [get_ports {adc_dco_p}]
set_property IOSTANDARD LVDS_25 [get_ports {adc_dco_n}]
set_property DIFF_TERM TRUE [get_ports {adc_dco_p}]
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# (Place 30-876). The schematic routes CLKOUT to C4; this cannot be
# changed without a board respin. The clock still uses an IBUFG and
# reaches the clock network — the constraint only disables the DRC check.
set_property PACKAGE_PIN C4 [get_ports {ft_clkout}]
set_property IOSTANDARD LVCMOS33 [get_ports {ft_clkout}]
create_clock -name ft_clkout -period 16.667 [get_ports {ft_clkout}]
set_input_jitter [get_clocks ft_clkout] 0.2
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# ============================================================================
# RESET (Active-Low)
# ============================================================================
# DIG_4 (STM32 PD12 → FPGA Bank 15 pin E15)
# STM32 firmware uses HAL_GPIO_WritePin to assert/deassert FPGA reset.

set_property PACKAGE_PIN E15 [get_ports {reset_n}]
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# set_property SLEW FAST [get_ports {dac_clk}]

# DAC Sleep Control — DAC_SLEEP net
set_property PACKAGE_PIN A15 [get_ports {dac_sleep}]
set_property IOSTANDARD LVCMOS33 [get_ports {dac_sleep}]

# RF Switch Control — M3S_VCTRL net
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# ============================================================================

# ADAR1000 TX Load Pins (via level shifters, active-high pulse)
set_property PACKAGE_PIN P3 [get_ports {adar_tx_load_1}]
set_property PACKAGE_PIN T4 [get_ports {adar_tx_load_2}]
set_property PACKAGE_PIN R3 [get_ports {adar_tx_load_3}]
set_property PACKAGE_PIN R2 [get_ports {adar_tx_load_4}]

# ADAR1000 RX Load Pins
set_property PACKAGE_PIN M5 [get_ports {adar_rx_load_1}]
set_property PACKAGE_PIN T2 [get_ports {adar_rx_load_2}]
set_property PACKAGE_PIN R1 [get_ports {adar_rx_load_3}]
set_property PACKAGE_PIN N4 [get_ports {adar_rx_load_4}]

# Bank 34 VCCO = 1.8V → must use LVCMOS18 (not LVCMOS33)
set_property IOSTANDARD LVCMOS18 [get_ports {adar_*_load_*}]

# ADAR1000 TR (Transmit/Receive) Pins
set_property PACKAGE_PIN N2 [get_ports {adar_tr_1}]
set_property PACKAGE_PIN N1 [get_ports {adar_tr_2}]
set_property PACKAGE_PIN P1 [get_ports {adar_tr_3}]
set_property PACKAGE_PIN P4 [get_ports {adar_tr_4}]
set_property IOSTANDARD LVCMOS18 [get_ports {adar_tr_*}]

# ============================================================================
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set_property IOSTANDARD LVCMOS33 [get_ports {stm32_*_3v3}]

# 1.8V Side (to ADAR1000, Bank 34, VCCO=1.8V)
set_property PACKAGE_PIN P5 [get_ports {stm32_sclk_1v8}]
set_property PACKAGE_PIN M1 [get_ports {stm32_mosi_1v8}]
set_property PACKAGE_PIN N3 [get_ports {stm32_miso_1v8}]
set_property PACKAGE_PIN L5 [get_ports {stm32_cs_adar1_1v8}]
set_property PACKAGE_PIN L4 [get_ports {stm32_cs_adar2_1v8}]
set_property PACKAGE_PIN M4 [get_ports {stm32_cs_adar3_1v8}]
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# ============================================================================
# STM32 CONTROL INTERFACE (DIG bus, Bank 15, VCCO=3.3V)
# ============================================================================
# DIG_0..DIG_4 are STM32 outputs (PD8-PD12) → FPGA inputs
# DIG_5..DIG_7 are STM32 inputs (PD13-PD15) ← FPGA outputs (unused in RTL)

set_property PACKAGE_PIN F13 [get_ports {stm32_new_chirp}]       ;# DIG_0 (PD8)
set_property PACKAGE_PIN E16 [get_ports {stm32_new_elevation}]   ;# DIG_1 (PD9)
set_property PACKAGE_PIN D16 [get_ports {stm32_new_azimuth}]     ;# DIG_2 (PD10)
set_property PACKAGE_PIN F15 [get_ports {stm32_mixers_enable}]   ;# DIG_3 (PD11)
set_property IOSTANDARD LVCMOS33 [get_ports {stm32_new_*}]
set_property IOSTANDARD LVCMOS33 [get_ports {stm32_mixers_enable}]
# reset_n is DIG_4 (PD12) — constrained above in the RESET section

# DIG_5 = H11, DIG_6 = G12, DIG_7 = H12 — FPGA→STM32 status outputs
# DIG_5: AGC saturation flag (PD13 on STM32)
# DIG_6: AGC enable flag (PD14) — mirrors FPGA host_agc_enable to STM32
# DIG_7: reserved (PD15)
set_property PACKAGE_PIN H11 [get_ports {gpio_dig5}]
set_property PACKAGE_PIN G12 [get_ports {gpio_dig6}]
set_property PACKAGE_PIN H12 [get_ports {gpio_dig7}]
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set_property DRIVE 8 [get_ports {ft_siwu}]
set_property DRIVE 8 [get_ports {ft_data[*]}]

# ft_clkout constrained above in CLOCK CONSTRAINTS section (C4, 60 MHz)

# --------------------------------------------------------------------------
# FT2232H Source-Synchronous Timing Constraints
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# ============================================================================
# The following RTL output ports have no corresponding FPGA pins in the
# schematic. The only FPGA→STM32 outputs available are DIG_5 (H11),
# DIG_6 (G12), and DIG_7 (H12) — only 3 pins for potentially 60+ signals.
#
# These constraints are commented out. If status readback is needed, either:
#   (a) Multiplex selected status bits onto DIG_5/6/7, or
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
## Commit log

2026-04-20 Upload local radar model and source code
